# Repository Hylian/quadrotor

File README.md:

quadrotor
=========

Quadrotor built from scratch

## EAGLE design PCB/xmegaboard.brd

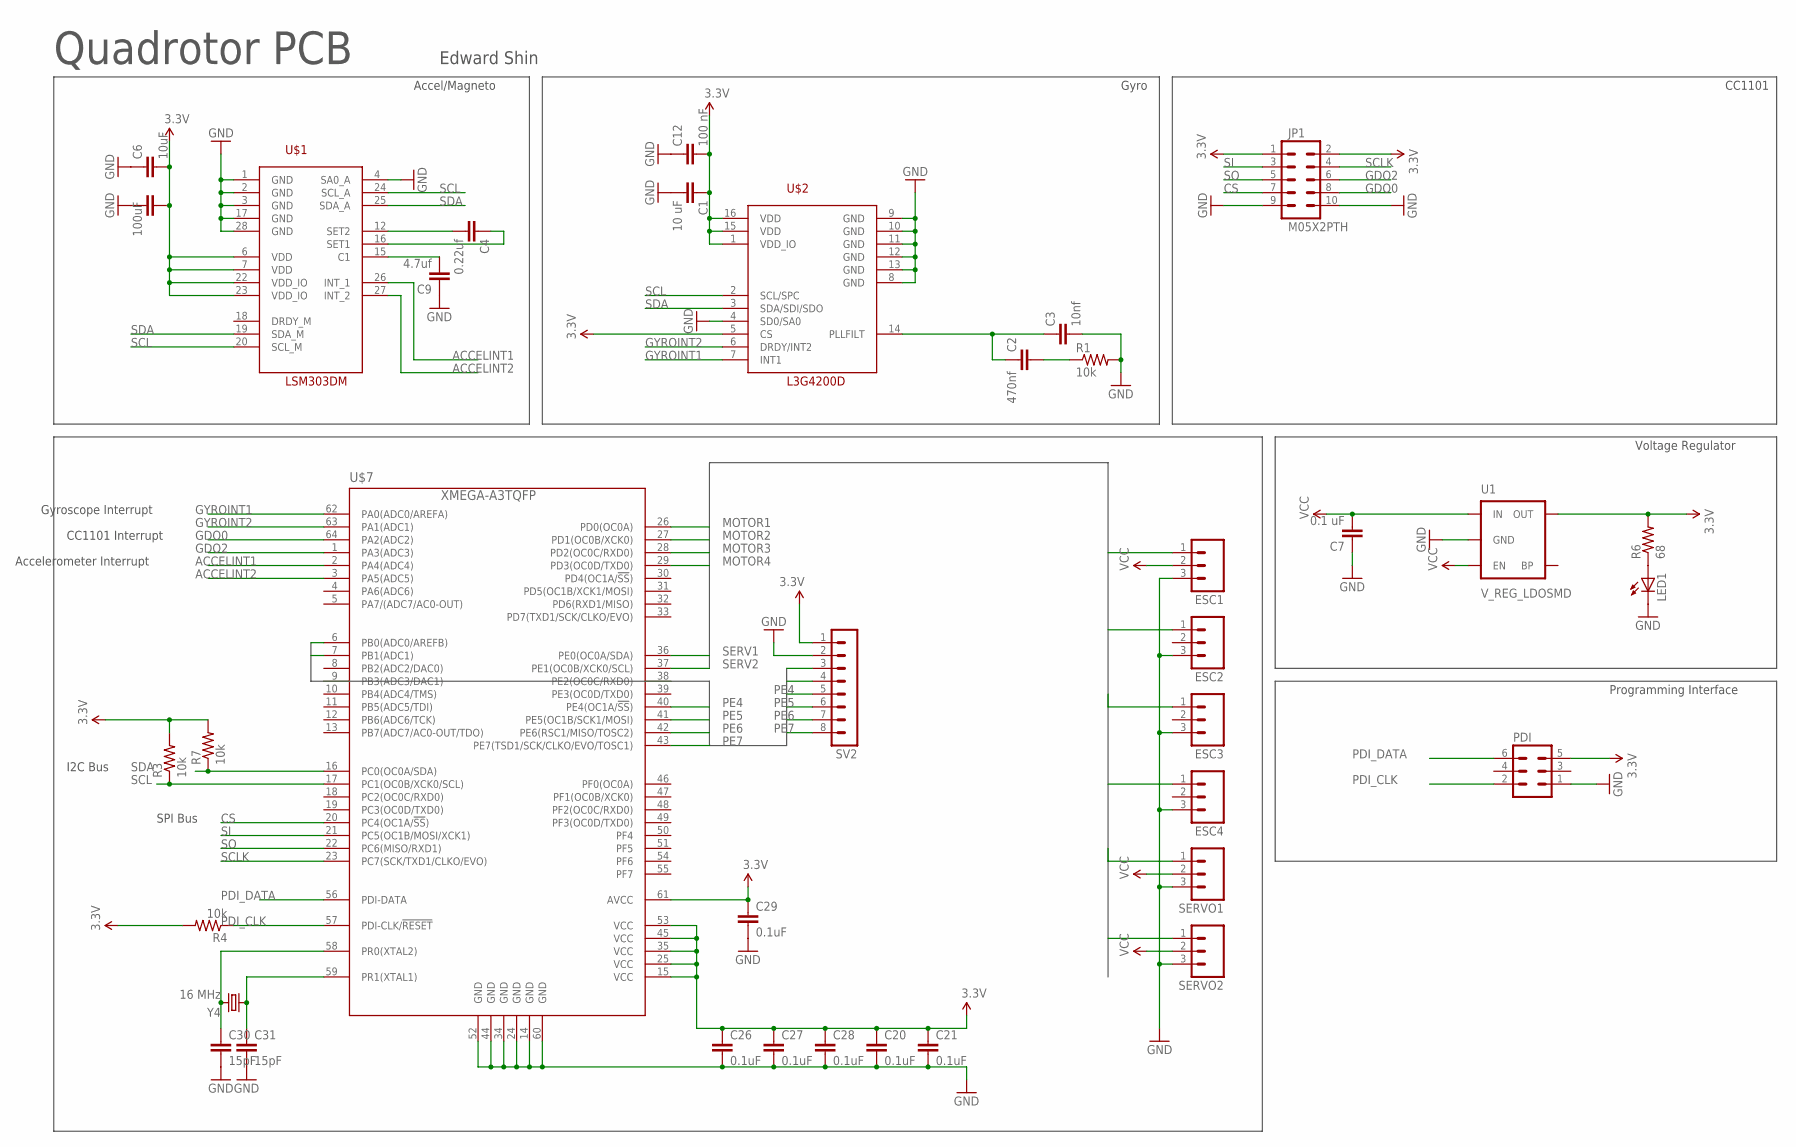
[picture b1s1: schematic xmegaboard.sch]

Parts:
C1: 10 uF; 0603-CAP
C2: 470nf; 0603-CAP
C3: 10nf; 0603-CAP
C4: 0.22uf; 0603-CAP
C5: 100uF; 0603-CAP
C6: 10uF; 0603-CAP
C7: 0.1 uF; 0603-CAP
C9: 4.7uf; 0603-CAP
C12: 100 nF; 0603-CAP
C20, C21, C26, C27, C28, C29: 0.1uF; 0603-CAP
C30, C31: 15pF; 0603-CAP
ESC1, ESC2, ESC3, ESC4: M03PTH; 1X03
JP1: M05X2PTH; AVR_ICSP
LED1: LED0603; LED-0603
PDI: MA03-2
R1, R3, R4, R7: 10k; 0603-RES
R6: 68; 0603-RES
SERVO1, SERVO2: M03PTH; 1X03
SV2: MA08-1
U1: V_REG_LDOSMD; SOT23-5
U$1: LSM303DM; LGA28-5X5
U$2: L3G4200D; LGA16-4X4
U$7: XMEGA-A3TQFP; TQFP64
Y4: 16 MHz; CRYSTAL-32KHZ-SMD

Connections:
3.3V: C1.1, C5.2, C6.2, C12.2, C20.1, C21.1, C26.1, C27.1, C28.1, C29.1, JP1.1, JP1.2, PDI.5, R3.2, R4.2, R6.2, R7.2, SV2.1, U1.5 (OUT), U$1.6 (VDD), U$1.7 (VDD), U$1.22 (VDD_IO), U$1.23 (VDD_IO), U$2.1 (VDD_IO), U$2.5 (CS), U$2.15 (VDD), U$2.16 (VDD), U$7.15 (VCC), U$7.25 (VCC), U$7.35 (VCC), U$7.45 (VCC), U$7.53 (VCC), U$7.61 (AVCC)
ACCELINT1: U$1.26 (INT_1), U$7.2 (PA4(ADC4))
ACCELINT2: U$1.27 (INT_2), U$7.3 (PA5(ADC5))
CS: JP1.7, U$7.20 (PC4(OC1A/!SS!))
GDO0: JP1.8, U$7.64 (PA2(ADC2))
GDO2: JP1.6, U$7.1 (PA3(ADC3))
GND: C1.2, C3.2, C5.1, C6.1, C7.1, C9.1, C12.1, C20.2, C21.2, C26.2, C27.2, C28.2, C29.2, C30.2, C31.2, ESC1.3, ESC2.3, ESC3.3, ESC4.3, JP1.9, JP1.10, LED1.C, PDI.1, R1.2, SERVO1.3, SERVO2.3, SV2.2, U1.2 (GND), U$1.1 (GND), U$1.2 (GND), U$1.3 (GND), U$1.4 (SA0_A), U$1.17 (GND), U$1.28 (GND), U$2.4 (SD0/SA0), U$2.8 (GND), U$2.9 (GND), U$2.10 (GND), U$2.11 (GND), U$2.12 (GND), U$2.13 (GND), U$7.14 (GND), U$7.24 (GND), U$7.34 (GND), U$7.44 (GND), U$7.52 (GND), U$7.60 (GND)
GYROINT1: U$2.7 (INT1), U$7.62 (PA0(ADC0/AREFA))
GYROINT2: U$2.6 (DRDY/INT2), U$7.63 (PA1(ADC1))
MOTOR1: ESC1.1, U$7.26 (PD0(OC0A))
MOTOR2: ESC2.1, U$7.27 (PD1(OC0B/XCK0))
MOTOR3: ESC3.1, U$7.28 (PD2(OC0C/RXD0))
MOTOR4: ESC4.1, U$7.29 (PD3(OC0D/TXD0))
unnamed: C2.1, C3.1, U$2.14 (PLLFILT)
unnamed: C2.2, R1.1
unnamed: C4.2, U$1.12 (SET2)
unnamed: C4.1, U$1.16 (SET1)
unnamed: C9.2, U$1.15 (C1)
unnamed: LED1.A, R6.1
unnamed: C30.1, U$7.58 (PR0(XTAL2)), Y4.X2 (2)
unnamed: C31.1, U$7.59 (PR1(XTAL1)), Y4.X1 (1)
PDI_CLK: PDI.2, R4.1, U$7.57 (PDI-CLK/!RESET)
PDI_DATA: PDI.6, U$7.56 (PDI-DATA)
PE2: SV2.3, U$7.6 (PB0(ADC0/AREFB))
PE3: SV2.4, U$7.7 (PB1(ADC1))
PE4: SV2.5, U$7.40 (PE4(OC1A/!SS!))
PE5: SV2.6, U$7.41 (PE5(OC1B/SCK1/MOSI))
PE6: SV2.7, U$7.42 (PE6(RSC1/MISO/TOSC2))
PE7: SV2.8, U$7.43 (PE7(TSD1/SCK/CLKO/EVO/TOSC1))
SCL: R3.1, U$1.20 (SCL_M), U$1.24 (SCL_A), U$2.2 (SCL/SPC), U$7.17 (PC1(OC0B/XCK0/SCL))
SCLK: JP1.4, U$7.23 (PC7(SCK/TXD1/CLKO/EVO))
SDA: R7.1, U$1.19 (SDA_M), U$1.25 (SDA_A), U$2.3 (SDA/SDI/SDO), U$7.16 (PC0(OC0A/SDA))
SERV1: SERVO1.1, U$7.36 (PE0(OC0A/SDA))
SERV2: SERVO2.1, U$7.37 (PE1(OC0B/XCK0/SCL))
SI: JP1.3, U$7.21 (PC5(OC1B/MOSI/XCK1))
SO: JP1.5, U$7.22 (PC6(MISO/RXD1))
VCC: C7.2, ESC1.2, SERVO1.2, SERVO2.2, U1.1 (IN), U1.3 (EN)

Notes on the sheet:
Accel/Magneto
Gyro
I2C Bus
SPI Bus
CC1101 Interrupt
CC1101
Voltage Regulator
Programming Interface
Quadrotor PCB
Accelerometer Interrupt
Gyroscope Interrupt
Edward Shin

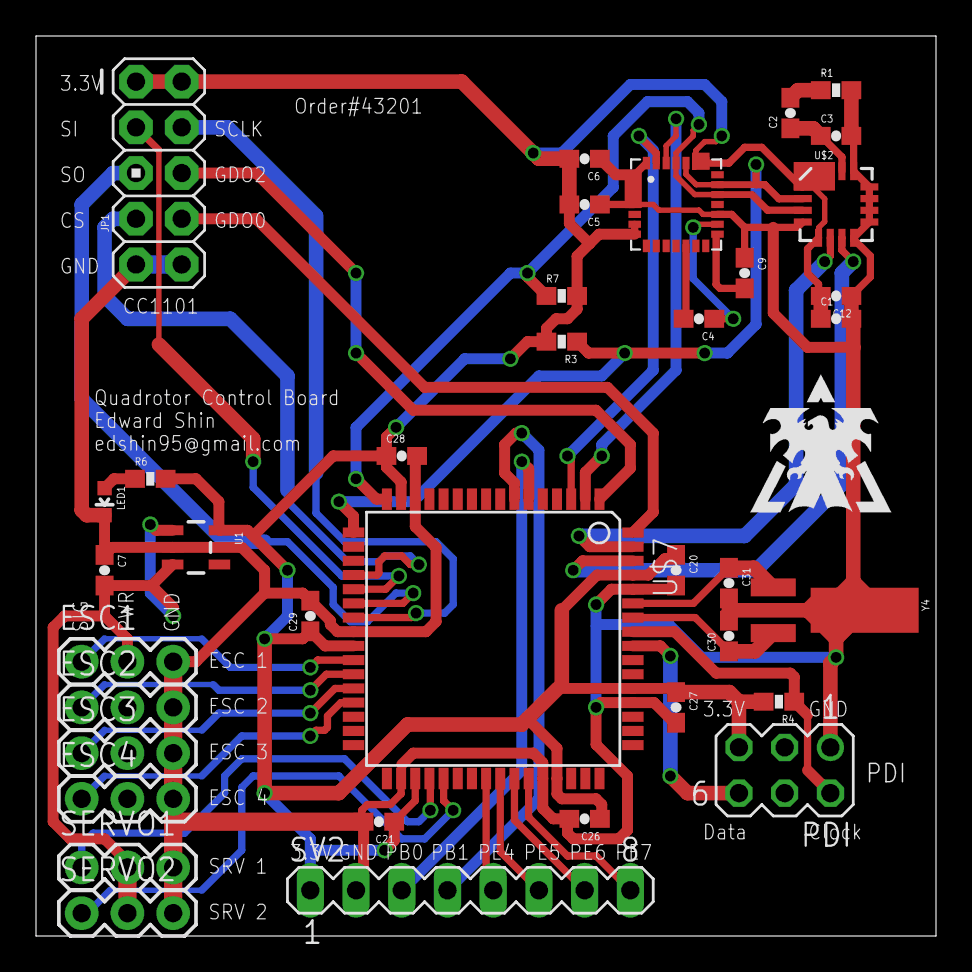
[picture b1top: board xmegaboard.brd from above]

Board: 2 copper layers, 50.0 x 50.0 mm, 37 parts (0 on the bottom side), 37 nets.

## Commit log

2013-06-27 added PCB files
2013-06-27 rm test.txt
2013-06-27 testing ssh keys
2013-06-27 removed
2013-06-27 Added Arduino code to test reading sensor values.
2013-06-28 Modified sensor testing code (all 3 axis of accel now return same value)
2013-06-28 Testing code for pulling accelerometer values.
2013-06-30 Began work on CC1101 driver port
2013-06-30 Finished naive functions for SPI with CC1101.
2013-06-30 Initial commit of core radio comm. functions.
2013-06-30 Changed register settings according to SmartRF and fixed trailing #endif
2013-07-01 Added IOPORT in ASF to fix SPI
2013-07-01 Moved radioCore to /src
2013-07-01 Needs full duplex transmission
2013-07-04 Fixed CC1101 driver to use duplex SPI correctly (gets the stat byte)
2013-07-04 matched function prototypes to actual functions
2013-07-05 project update
2013-07-06 Added TWI initialize function
2013-07-06 Changed TWICfg to be initialized only once (#ifndef)
2013-07-09 TWI read/write library initial commit
2013-07-09 swapped around the order of the two addresses the functions ask for
2013-07-29 modified twiWrite() to take in the send data directly
    TODO: Check with the ASF docs to see if i'm doing the pointer stuff
    right
2013-07-29 fixed a typo in twiWrite()
2013-07-29 Accel library initial commit; defined registers and initialize/read functions
2013-07-29 Renamed Accel.c to LSM303D to reflect both accel and magnet capabilities
2013-07-29 added include file for LSM303D library
2013-07-29 Updated TWI.h function prototype to match TWI.c
2013-07-29 Initial commit of gyro library
2013-07-29 Changed WHO_AM_I define to avoid collision
    The other register definitions don't collide
2013-07-29 Fixed pointers
2013-07-29 Changed unsupported binary format to hexadecimal
2013-07-29 Initial commit of motor/PWM library
2013-07-30 Fixed quotes around include file
2013-08-24 Kalman library initial commit
2013-08-24 PID library initial commit
2013-08-24 main.c initial control template
2013-08-24 initial commit of radio command interpreter
2013-08-24 fixed PID library to take in PIDobject pointers
2013-08-24 added radiocommand
2013-10-31 fixed ptrs
